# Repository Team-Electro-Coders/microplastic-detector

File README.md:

# SIH_Microplastic_Detector_by_Team_Electro_Coders

Welcome to the repository for the **Microplastic Detector Project**, developed by Team Electro Coders!

This repository contains three distinct versions of our real-time microplastic detection system, evolving from a basic proof-of-concept using an Arduino to an advanced, web-enabled system utilizing an ESP32 microcontroller.

---

## Project Overview

The core goal of this project is to create a real-time system that combines **computer vision (OpenCV)** with embedded hardware (Arduino/ESP32) to automatically identify and alert users about microplastic particles in a video stream.

---

## Repository Structure

The project's evolution is documented and implemented across three version folders:

| Folder | Version | Core Hardware | Key Focus |
| :--- | :--- | :--- | :--- |
| **MicroPlastic\_Detector\_V1.0** | **V1.0 (Basic)** | Arduino Uno | Simple real-time detection and LCD status display via serial communication. |
| **MicroPlastic\_Detector\_V2.0** | **V2.0 (Complete)** | Arduino Uno | Enhanced system with **Machine Learning (TensorFlow)** for particle type classification and a comprehensive calibration and data collection workflow. |
| **MicroPlastic\_Detector\_V3.0** | **V3.0 (Enhanced/Web)** | ESP32 DevKit | Hybrid system featuring Wi-Fi connectivity, a **live web dashboard (Flask)**, data logging, and scale calibration, using the ESP32 for local control and the PC for heavy processing. |

---

## Version Summaries & Features

### 1. MicroPlastic\_Detector\_V1.0 (Basic)

This is the initial, straightforward implementation focusing on proving the concept of computer vision-based detection communicating with embedded hardware.

| Component | Technology/Hardware | Function |
| :--- | :--- | :--- |
| **Detection** | Python, OpenCV | [cite_start]Detects bright particles (simulating microplastics) using image processing (grayscale, blur, thresholding, contour detection). [cite: 4, 5, 95, 97, 99, 100, 101] |
| **Hardware** | Arduino Uno, 16x2 LCD | [cite_start]Receives status via **Serial communication** and displays "Detected! :)" or "Clean :)" on the LCD. [cite: 2, 4, 5, 104] |
| **Alert** | LCD Display | [cite_start]Real-time status update based on the particle count exceeding a configurable threshold (`PARTICLE_THRESHOLD`). [cite: 65, 80, 81, 139] |
| **Customization** | Python Script | [cite_start]Sensitivity can be adjusted via `PARTICLE_THRESHOLD` and area thresholds in the contour detection code. [cite: 65, 84, 87] |

---

### 2. MicroPlastic\_Detector\_V2.0 (Complete Implementation)

Version 2.0 transforms the basic detector into a comprehensive, research-ready system by integrating machine learning for microplastic *type classification* (e.g., fiber, fragment, bead) and a structured calibration process.

| Feature | Technologies Used | Benefit |
| :--- | :--- | :--- |
| **Classification** | **TensorFlow**, **Keras** | [cite_start]Trains a model (`train_type_classifier.py`) to categorize detected particles into types like **fiber**, **fragment**, **film**, and **bead**. [cite: 473, 489, 512, 513, 514, 515, 586] |
| **Enhanced Files** | Python Scripts (e.g., `final_detector.py`, `calibrate_concentration.py`) | [cite_start]Includes enhanced scripts for detection, training, collection, and advanced concentration **calibration** for scientific validation. [cite: 538, 539, 540, 541, 602, 603] |
| **Data Workflow** | `dataset/` and `logs/` folders | [cite_start]Structured process for manual sample collection, labeling, model training, and saving results/logs. [cite: 509, 532, 565, 570] |
| **Hardware** | Arduino Uno, 16x2 LCD | [cite_start]Maintains the reliable serial communication interface for real-time status display. [cite: 435, 436] |

---

### 3. MicroPlastic\_Detector\_V3.0 (Enhanced/Web)

This version introduces an **ESP32** for connectivity and a web interface, moving towards a more modern, accessible, and data-focused platform. The Arduino serial communication is replaced with a robust Wi-Fi communication protocol.

| Feature | Technologies/Components | Benefit |
| :--- | :--- | :--- |
| **Hardware** | **ESP32 DevKit**, **I2C LCD** | [cite_start]ESP32 handles Wi-Fi, local control, and a simpler I2C LCD, improving portability and power efficiency compared to Arduino's direct serial connection. [cite: 151, 158, 201, 202, 396] |
| **Web Interface** | **Flask Web Server** | [cite_start]Provides a **Live web dashboard** at `http://localhost:5000` with real-time video, statistics, charts, and particle size histograms. [cite: 154, 179, 293, 323, 324, 325] |
| **Data Management** | CSV Logging, REST API | [cite_start]Supports automatic **CSV data logging and export** (`data_logger.py`) and uses API endpoints for fetching stats and history. [cite: 155, 184, 347, 352, 355] |
| **Calibration** | Scale Calibration Mode | [cite_start]Offers a dedicated calibration mode (`python main.py --calibrate`) to automatically calculate the pixel-to-millimeter scale factor for accurate particle sizing. [cite: 159, 273, 309, 311, 316] |
| **Configuration** | `config.json` | [cite_start]Centralized, easy-to-edit JSON file for configuring ESP32 connection, camera settings, and detection parameters. [cite: 164, 257] |

---

## How to Get Started

To begin working with any version, navigate to the respective folder and refer to its internal documentation (or the full PDF guides provided) for detailed setup and usage instructions.

1.  **Select a Version:** Choose the folder corresponding to the system you wish to set up (V1.0, V2.0, or V3.0).
2.  **Review Requirements:** Check the **Hardware** and **Software Requirements** section in the version's documentation.
3.  **Setup Environment:** Install the required Python packages (e.g., OpenCV, NumPy, PySerial) and set up the Arduino/ESP32 IDE with necessary libraries.
4.  **Configure & Run:**
    * **V1.0/V2.0:** Update `VIDEO_SOURCE` and `ARDUINO_PORT` in the Python script (`final_detector.py`).
    * **V3.0:** Edit the settings in `config.json`.
    * Run the main Python script.

### Example Installation (V1.0 - Python Dependencies):

```bash
# Recommended for V1.0 - also useful as a base for V2.0/V3.0
pip install opencv-python numpy pyserial

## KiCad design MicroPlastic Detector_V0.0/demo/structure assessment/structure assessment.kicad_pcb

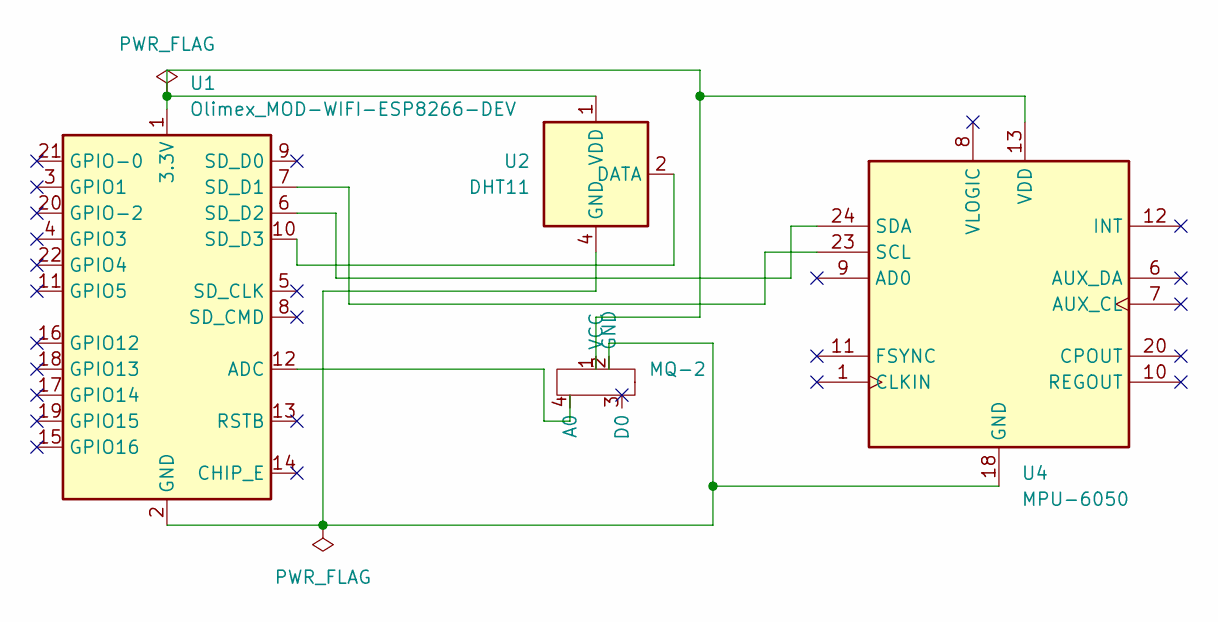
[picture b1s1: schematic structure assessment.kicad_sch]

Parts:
MQ-2: MQ-6
U1: Olimex_MOD-WIFI-ESP8266-DEV
U2: DHT11; Aosong_DHT11_5.5x12.0_P2.54mm
U4: MPU-6050; InvenSense_QFN-24_4x4mm_P0.5mm

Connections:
unnamed: MQ-2.4 (A0), U1.12 (ADC)
unnamed: MQ-2.2 (GND), U1.2 (GND), U2.4 (GND), U4.18 (GND)
unnamed: MQ-2.1 (VCC), U1.1 (3.3V), U2.1 (VDD), U4.13 (VDD)
unnamed: U1.7 (SD_D1), U4.23 (SCL)
unnamed: U1.6 (SD_D2), U4.24 (SDA)
unnamed: U1.10 (SD_D3), U2.2 (DATA)

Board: 2 copper layers, 4 parts (0 on the bottom side), 6 nets, no tracks yet.

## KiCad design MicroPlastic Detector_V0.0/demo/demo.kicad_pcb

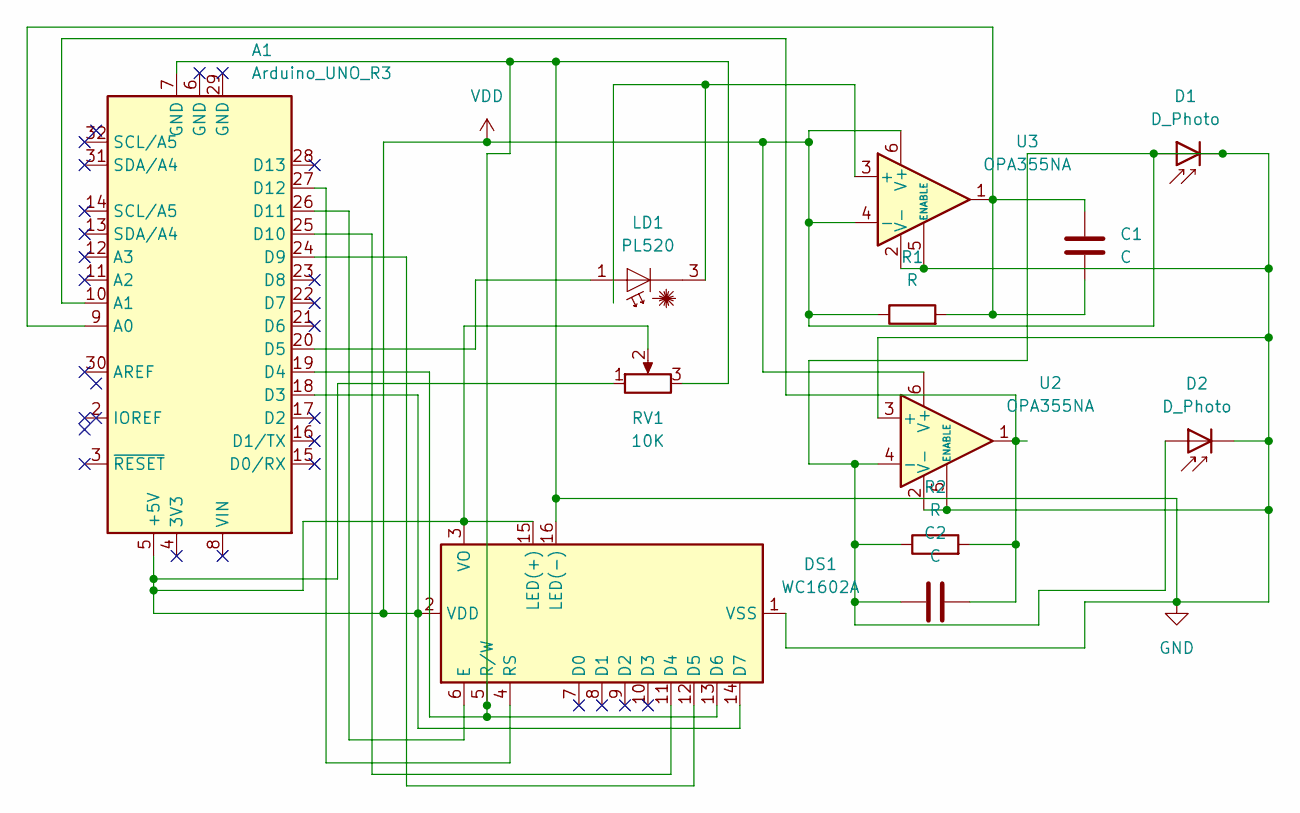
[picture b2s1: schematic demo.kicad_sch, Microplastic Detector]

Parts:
A1: Arduino_UNO_R3
C1, C2: C; CP_Elec_4x3.9
D1, D2: D_Photo; D_0402_1005Metric
DS1: WC1602A
LD1: PL520; LaserDiode_TO38ICut-3
R1, R2: R; R_0402_1005Metric_Pad0.72x0.64mm_HandSolder
RV1: 10K; Potentiometer_ACP_CA14-VSMD_Vertical_Hole
U2, U3: OPA355NA; SOT-23-6

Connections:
GND: A1.5 (+5V), A1.7 (GND), A1.18 (D3), A1.19 (D4), C2.1, D1.1 (K), D1.2 (A), D2.1 (K), D2.2 (A), DS1.1 (VSS), DS1.2 (VDD), DS1.3 (VO), DS1.5 (R/W), DS1.13 (D6), DS1.14 (D7), DS1.15 (LED(+)), DS1.16 (LED(-)), R1.1, R2.1, RV1.1, RV1.2, RV1.3, U2.2 (V-), U2.3 (+), U2.4 (-), U2.5 (ENABLE), U2.6 (V+), U3.2 (V-), U3.4 (-), U3.5 (ENABLE), U3.6 (V+)
unnamed: A1.9 (A0), C1.1, C1.2, R1.2, U3.1
unnamed: A1.10 (A1), C2.2, R2.2, U2.1
unnamed: A1.20 (D5), LD1.1 (A)
unnamed: A1.24 (D9), DS1.12 (D5)
unnamed: A1.25 (D10), DS1.11 (D4)
unnamed: A1.26 (D11), DS1.6 (E)
unnamed: A1.27 (D12), DS1.4 (RS)
unnamed: LD1.3 (C), U3.3 (+)

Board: 2 copper layers, 12 parts (0 on the bottom side), 9 nets, no tracks yet.

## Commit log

2026-05-27 Add PCB
